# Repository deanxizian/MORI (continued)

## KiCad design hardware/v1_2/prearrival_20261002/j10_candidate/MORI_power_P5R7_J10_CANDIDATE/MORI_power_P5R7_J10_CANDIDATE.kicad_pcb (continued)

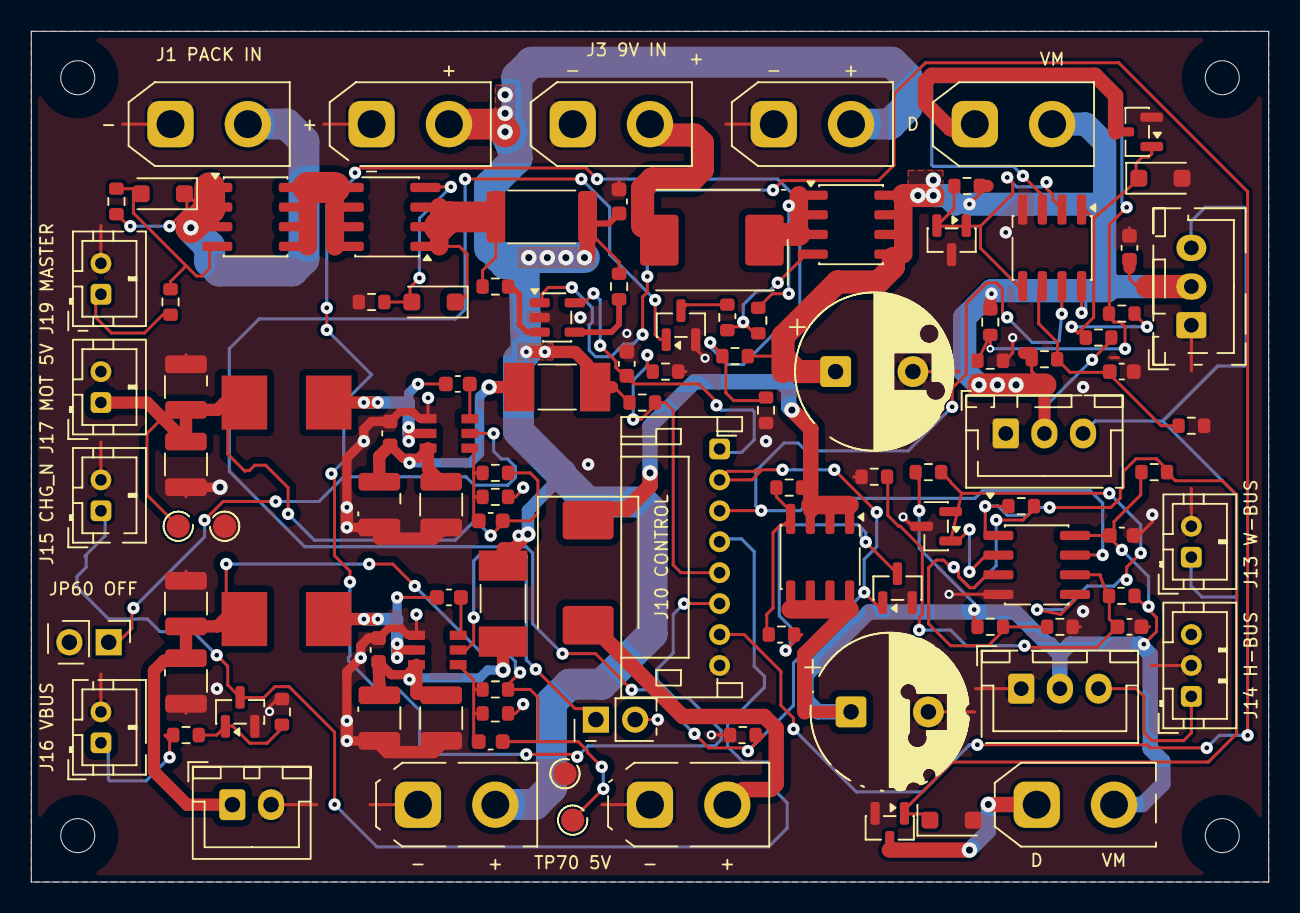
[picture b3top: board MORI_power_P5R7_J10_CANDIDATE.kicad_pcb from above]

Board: 4 copper layers, 80.0 x 55.0 mm, 112 parts (0 on the bottom side), 53 nets.

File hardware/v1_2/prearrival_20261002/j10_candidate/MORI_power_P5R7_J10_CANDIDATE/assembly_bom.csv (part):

ref,value,footprint,source,note
J1,PACK AFTER 6.3A FUSE,MORI_Custom:AMASS_XT30UPB-M_1x02_P5.0mm_Vertical__P3_J1,,Protected finished3S pack through external6.3A fuse. On-board Q90 is controlled by rear SW1. No direct small-switch load current.
J2,WHEEL BUCK VIN,MORI_Custom:AMASS_XT30UPB-M_1x02_P5.0mm_Vertical__P3_J2__P5_J2,,"AMASS XT30UPB-M PCB: pin1 minus, pin2 plus; mating housing polarization plus continuity check mandatory."
J3,WHEEL BUCK 9V RETURN,MORI_Custom:AMASS_XT30UPB-M_1x02_P5.0mm_Vertical__P3R1_J3,,"AMASS XT30UPB-M PCB: pin1 minus, pin2 plus; mating housing polarization plus continuity check mandatory."
J4,HEAD BUCK VIN,MORI_Custom:AMASS_XT30UPB-M_1x02_P5.0mm_Vertical__P2_J4__P3_J4__P3R1_J4,,"AMASS XT30UPB-M PCB: pin1 minus, pin2 plus; mating housing polarization plus continuity check mandatory."
J5,HEAD BUCK 6V RETURN,MORI_Custom:AMASS_XT30UPB-M_1x02_P5.0mm_Vertical__P2_J5__P3_J5__P5_J5,,"AMASS XT30UPB-M PCB: pin1 minus, pin2 plus; mating housing polarization plus continuity check mandatory."
J6,BAT_MON SERVICE / DNP,MORI_Custom:AMASS_XT30UPB-M_1x02_P5.0mm_Vertical__P3_J6__P3R1_J6,,Legacy external5V feed no longer used. Not5V. Leave unpopulated in S3.
J11,WHEEL DUMP 5R6 EXTERNAL,MORI_Custom:AMASS_XT30UPB-M_1x02_P5.0mm_Vertical__P5R5_DUMP,,"AMASS XT30UPB-M PCB: pin1 minus, pin2 plus; mating housing polarization plus continuity check mandatory."
J12,HEAD DUMP 10R EXTERNAL,MORI_Custom:AMASS_XT30UPB-M_1x02_P5.0mm_Vertical__P2_J12__P5_J12__P5R5_DUMP,,"AMASS XT30UPB-M PCB: pin1 minus, pin2 plus; mating housing polarization plus continuity check mandatory."
J7,S288 L,MORI_Custom:JST_XH_B3B-XH-A_1x03_P2.50mm_Vertical__P2_J7__P3_J7__P5_J7,,Board-side XH 3-pin interface only. SCS original 5264-3P uses 1GND/2VCC/3TTL. S288 factory mating plug remains unverified; adapter harness must be confirmed.
J8,S288 R,MORI_Custom:JST_XH_B3B-XH-A_1x03_P2.50mm_Vertical__P2_J8__P5_J8,,Board-side XH 3-pin interface only. SCS original 5264-3P uses 1GND/2VCC/3TTL. S288 factory mating plug remains unverified; adapter harness must be confirmed.
J9,SCS0009 CHAIN,MORI_Custom:JST_XH_B3B-XH-A_1x03_P2.50mm_Vertical__P5_J9,,Board-side XH 3-pin interface only. SCS original 5264-3P uses 1GND/2VCC/3TTL. S288 factory mating plug remains unverified; adapter harness must be confirmed.
J10,MOTION CONTROL,Connector_JST:JST_PH_S8B-PH-K_1x08_P2.00mm_Horizontal__MORI_1p35land_0p75drill,https://www.jst-mfg.com/product/pdf/eng/ePH.pdf,P4 PH 2.0 mm. PHR-8 / SPH-002T-P0.5S. Signal pin numbering unchanged. Check both mating views; never wire by color alone.
J13,S288 DATA,MORI_Custom:JST_PH_B2B-PH-K_1x02_P2.00mm_Vertical__P4_PH_ANNULUS,https://www.jst-mfg.com/product/pdf/eng/ePH.pdf,P4 PH 2.0 mm. PHR-2 / SPH-002T-P0.5S. Signal pin numbering unchanged. Check both mating views; never wire by color alone.
J14,HEAD DATA,MORI_Custom:JST_PH_B3B-PH-K_1x03_P2.00mm_Vertical__P4_PH_ANNULUS,https://www.jst-mfg.com/product/pdf/eng/ePH.pdf,P4 PH 2.0 mm. PHR-3 / SPH-002T-P0.5S. Signal pin numbering unchanged. Check both mating views; never wire by color alone.
J15,CHARGE INTERLOCK,MORI_Custom:JST_PH_B2B-PH-K_1x02_P2.00mm_Vertical__P4_PH_ANNULUS__P3R1_J15,https://www.jst-mfg.com/product/pdf/eng/ePH.pdf,P4 PH 2.0 mm. PHR-2 / SPH-002T-P0.5S. Signal pin numbering unchanged. Check both mating views; never wire by color alone.
J16,CHARGER RAW VBUS SENSE,MORI_Custom:JST_PH_B2B-PH-K_1x02_P2.00mm_Vertical__P4_PH_ANNULUS__P3R1_J16,https://www.jst-mfg.com/product/pdf/eng/ePH.pdf,P4 PH 2.0 mm. PHR-2 / SPH-002T-P0.5S. Signal pin numbering unchanged. Check both mating views; never wire by color alone.
Q1,AO4407A,MORI_Custom:SOIC-8_3.9x4.9mm_P1.27mm__P5_Q1,https://www.aosmd.com/sites/default/files/res/datasheets/AO4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,
R1,10k,Resistor_SMD:R_0603_1608Metric,,
D1,"BZT52H-C10,115",Diode_SMD:D_SOD-123F,,
R2,WSL2512R0100FEA 10mR 1% 1W,Resistor_SMD:R_2512_6332Metric,,
U1,INA180A1IDBVR,MORI_Custom:SOT-23-5__P5_U1,https://www.ti.com/lit/ds/symlink/ina180.pdf,Kelvin sense of 10mR; gain20 =>0.2V/A. Discharge only; reverse current not measured.
R3,0,Resistor_SMD:R_0603_1608Metric,,
R4,0,Resistor_SMD:R_0603_1608Metric,,
D10,B540C-13-F,MORI_Custom:D_SMC__P3_D10__P5_D10,https://www.diodes.com/datasheet/download/B540C.pdf,B540C-13-F verified from DS13012 Rev18-2; SMC cathode pin1. Thermal/quote NOT_QUALIFIED.
Q10,AO4407A,Package_SO:SOIC-8_3.9x4.9mm_P1.27mm,https://www.aosmd.com/sites/default/files/res/datasheets/AO4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,
Q11,AO3400A,MORI_Custom:SOT-23__P5_Q11,https://www.aosmd.com/sites/default/files/res/datasheets/AO3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,
R10,10k,MORI_Custom:R_0603_1608Metric__P5_R10,,
R11,100,MORI_Custom:R_0603_1608Metric__P5_R11,,
C10,Panasonic EEU-FR1C102 1000uF 16V,MORI_Custom:CP_Radial_D10.0mm_P5.00mm__P2_C10__P3_C10__P5_C10,,"D10 x H16; height is vendor capacitor envelope, NOT fitted into old10mm allocation."
D30,B540C-13-F,MORI_Custom:D_SMC__P5_D30,https://www.diodes.com/datasheet/download/B540C.pdf,B540C-13-F verified from DS13012 Rev18-2; SMC cathode pin1. Thermal/quote NOT_QUALIFIED.
Q30,AO4407A,MORI_Custom:SOIC-8_3.9x4.9mm_P1.27mm__P5_Q30,https://www.aosmd.com/sites/default/files/res/datasheets/AO4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,
Q31,AO3400A,Package_TO_SOT_SMD:SOT-23,https://www.aosmd.com/sites/default/files/res/datasheets/AO3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,
R30,10k,Resistor_SMD:R_0603_1608Metric,,
R31,100,MORI_Custom:R_0603_1608Metric__P5_R31,,
C30,Panasonic EEU-FR1C102 1000uF 16V,MORI_Custom:CP_Radial_D10.0mm_P5.00mm__P3_C30__P5_C30,,"D10 x H16; height is vendor capacitor envelope, NOT fitted into old10mm allocation."
U20,LM393BDR,MORI_Custom:SOIC-8_3.9x4.9mm_P1.27mm__P5_U20,https://www.ti.com/lit/ds/symlink/lm393b.pdf,
U21,TL431BIDBZR,Package_TO_SOT_SMD:SOT-23,https://www.ti.com/lit/ds/symlink/tl431.pdf,"DBZ pin1 cathode,2 reference,3 anode. B grade +/-0.5% at25C; thermal error in tolerance model."
Q20,AO3400A,Package_TO_SOT_SMD:SOT-23,https://www.aosmd.com/sites/default/files/res/datasheets/AO3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,
D20,"BZT52H-C10,115",Diode_SMD:D_SOD-123F,,
R20,2.2k,Resistor_SMD:R_0603_1608Metric,,
R21,33.2k 0.1%,Resistor_SMD:R_0603_1608Metric,,
R22,10k 0.1%,MORI_Custom:R_0603_1608Metric__P5_R22,,
R23,1M 0.1%,Resistor_SMD:R_0603_1608Metric,,
R24,2.2k,Resistor_SMD:R_0603_1608Metric,,
R25,37.4k 0.1%,Resistor_SMD:R_0603_1608Metric,,
R26,10k 0.1%,Resistor_SMD:R_0603_1608Metric,,
C20,100n,Capacitor_SMD:C_0603_1608Metric,,
C21,10n,Capacitor_SMD:C_0603_1608Metric,,
U40,LM393BDR,MORI_Custom:SOIC-8_3.9x4.9mm_P1.27mm__P5_U40,https://www.ti.com/lit/ds/symlink/lm393b.pdf,
U41,TL431BIDBZR,MORI_Custom:SOT-23__P5_U41,https://www.ti.com/lit/ds/symlink/tl431.pdf,"DBZ pin1 cathode,2 reference,3 anode. B grade +/-0.5% at25C; thermal error in tolerance model."
Q40,AO3400A,Package_TO_SOT_SMD:SOT-23,https://www.aosmd.com/sites/default/files/res/datasheets/AO3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,
D40,"BZT52H-C10,115",MORI_Custom:D_SOD-123F__P5_D40,,
R40,2.2k,Resistor_SMD:R_0603_1608Metric,,
R41,16.5k 0.1%,Resistor_SMD:R_0603_1608Metric,,
R42,10k 0.1%,Resistor_SMD:R_0603_1608Metric,,
R43,1M 0.1%,Resistor_SMD:R_0603_1608Metric,,
R44,2.2k,Resistor_SMD:R_0603_1608Metric,,
R45,18.7k 0.1%,MORI_Custom:R_0603_1608Metric__P5_R45,,
R46,10k 0.1%,Resistor_SMD:R_0603_1608Metric,,
C40,100n,MORI_Custom:C_0603_1608Metric__P5_C40,,
C41,10n,Capacitor_SMD:C_0603_1608Metric,,
R50,100k 0.1%,Resistor_SMD:R_0603_1608Metric,,
R51,27k 0.1%,Resistor_SMD:R_0603_1608Metric,,
R52,100k 0.1%,Resistor_SMD:R_0603_1608Metric,,
R53,27k 0.1%,Resistor_SMD:R_0603_1608Metric,,
R54,10k,MORI_Custom:R_0603_1608Metric__P5_R54,,
R55,47k,Resistor_SMD:R_0603_1608Metric,,
R56,100k,MORI_Custom:R_0603_1608Metric__P5_R56,,
C1,100n,Capacitor_SMD:C_0603_1608Metric,,
C2,1u 25V,MORI_Custom:C_0603_1608Metric__P3_C2,,
Q50,MMBT3904LT1G,MORI_Custom:SOT-23__P5_Q50,,SOT23 1B 2E 3C. Raw VBUS detect only; neither CC nor charging control.
H1,M2 mounting / POSITION TBD,MountingHole:MountingHole_2.2mm_M2,,
H2,M2 mounting / POSITION TBD,MountingHole:MountingHole_2.2mm_M2,,
H3,M2 mounting / POSITION TBD,MountingHole:MountingHole_2.2mm_M2,,
H4,M2 mounting / POSITION TBD,MountingHole:MountingHole_2.2mm_M2,,
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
